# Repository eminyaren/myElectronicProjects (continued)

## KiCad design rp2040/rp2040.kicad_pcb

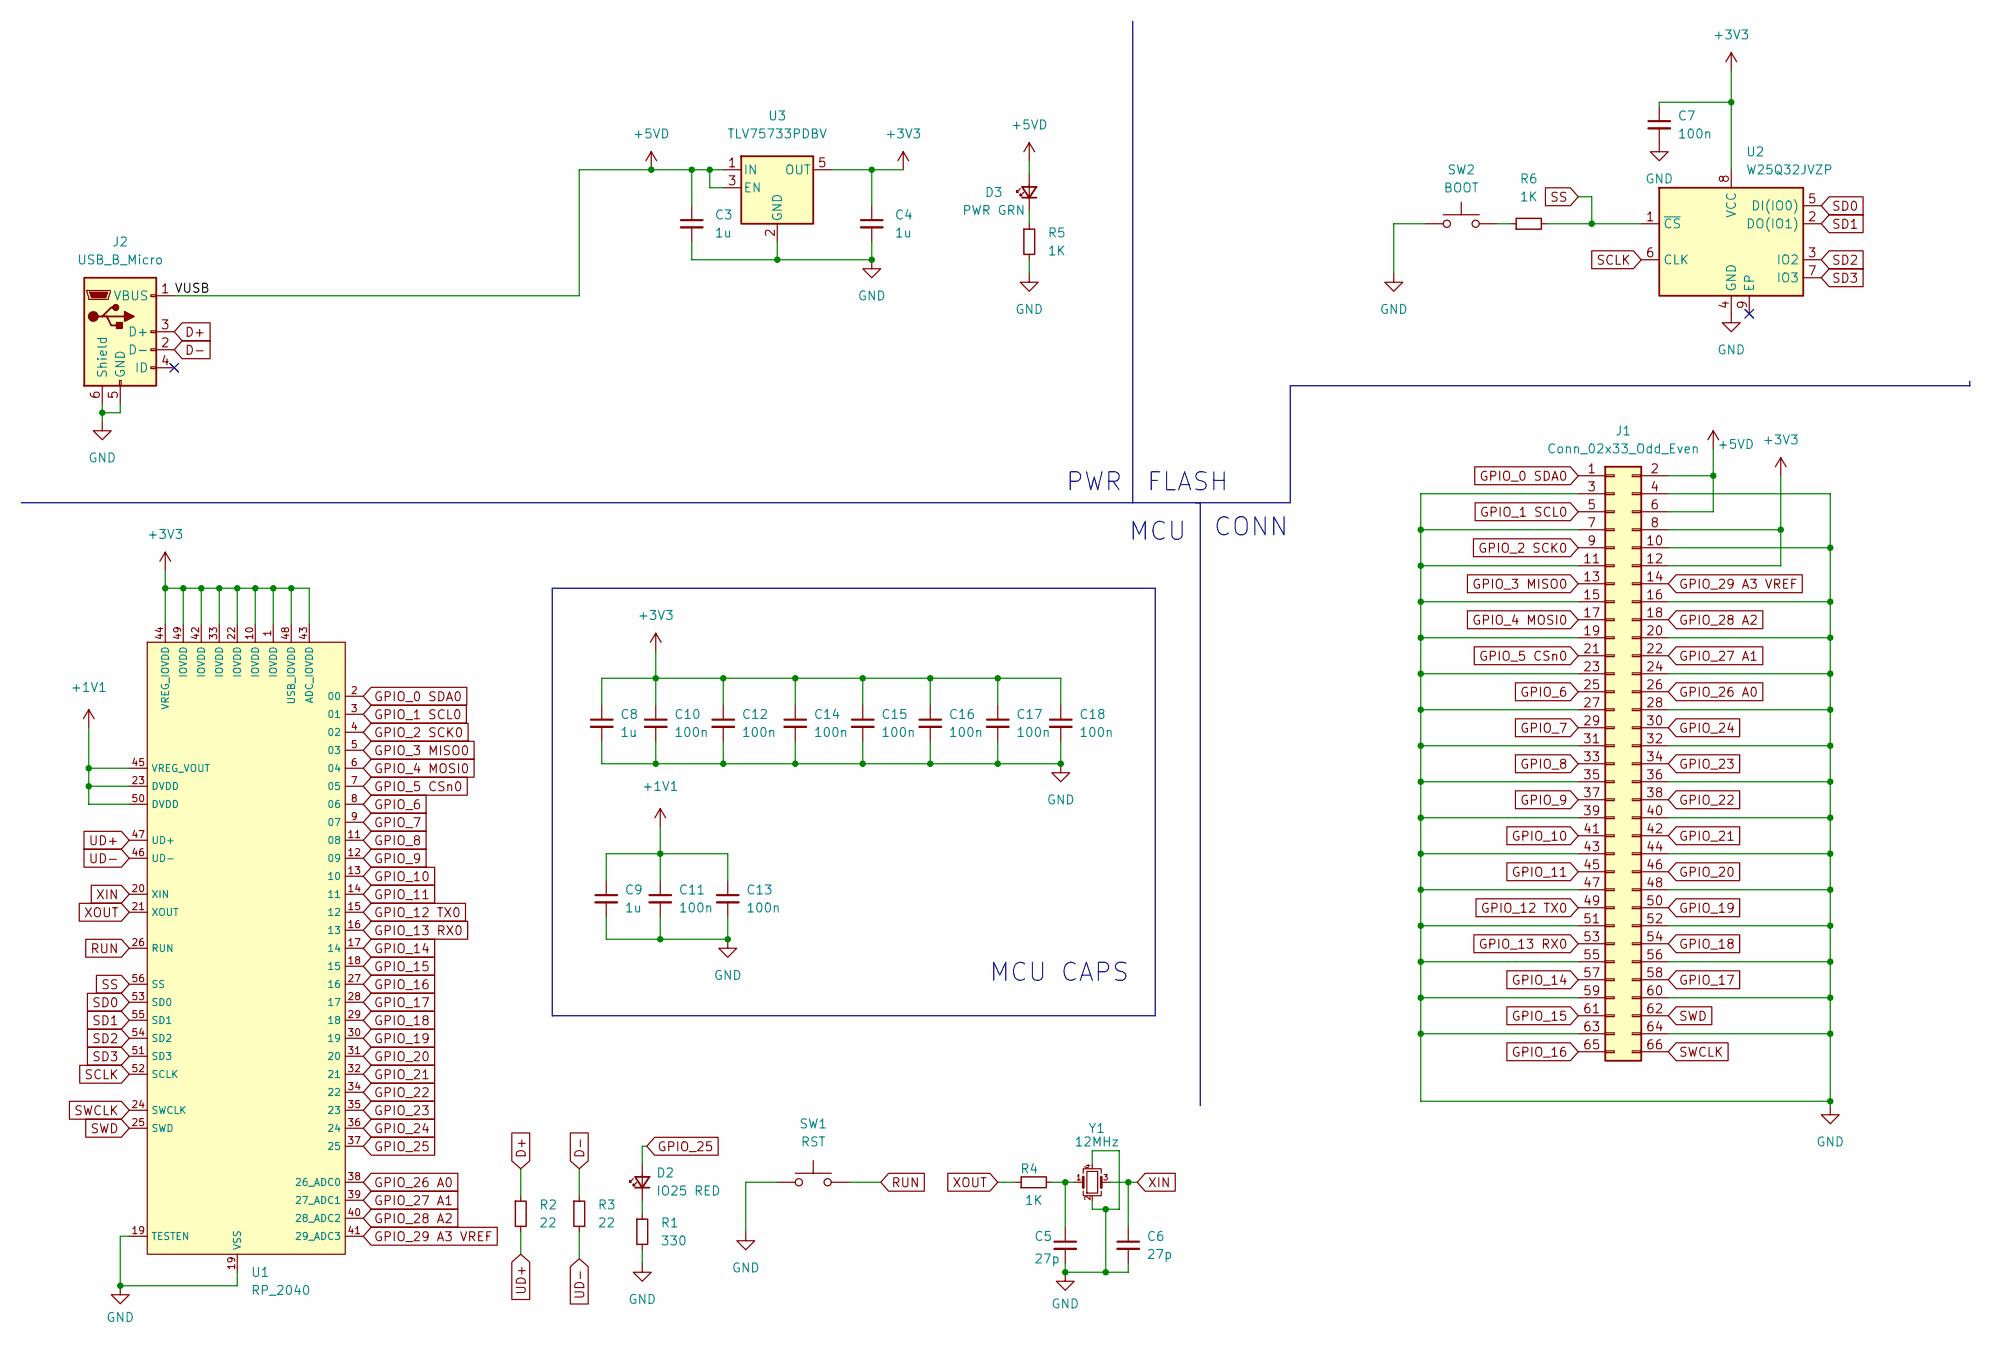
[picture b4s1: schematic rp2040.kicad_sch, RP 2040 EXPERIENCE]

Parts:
C3, C4: 1u; CP_EIA-1608-08_AVX-J
C5, C6: 27p; C_0402_1005Metric
C7, C10, C11, C12, C13, C14, C15, C16, C17, C18: 100n; C_0402_1005Metric
C8, C9: 1u; C_0603_1608Metric
D2: IO25 RED; LED_0201_0603Metric
D3: PWR GRN; LED_0201_0603Metric
J1: Conn_02x33_Odd_Even; PinHeader_2x33_P2.54mm_Horizontal
J2: USB_B_Micro; USB_Micro-B_Molex_47346-0001
R1: 330; R_0402_1005Metric
R2, R3: 22; R_0402_1005Metric
R4, R5, R6: 1K; R_0402_1005Metric
SW1: RST; SW_Push_SPST_NO_Alps_SKRK
SW2: BOOT; SW_Push_SPST_NO_Alps_SKRK
U1: RP_2040
U2: W25Q32JVZP; WSON-8-1EP_6x5mm_P1.27mm_EP3.4x4.3mm
U3: TLV75733PDBV; SOT-23-5
Y1: 12MHz; Crystal_SMD_3225-4Pin_3.2x2.5mm

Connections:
+1V1: C9.1, C11.1, C13.1, U1.23 (DVDD), U1.45 (VREG_VOUT), U1.50 (DVDD)
+3V3: C4.1, C7.1, C8.1, C10.1, C12.1, C14.1, C15.1, C16.1, C17.1, C18.1, J1.8, J1.12, U1.1 (IOVDD), U1.10 (IOVDD), U1.22 (IOVDD), U1.33 (IOVDD), U1.42 (IOVDD), U1.43 (ADC_IOVDD), U1.44 (VREG_IOVDD), U1.48 (USB_IOVDD), U1.49 (IOVDD), U2.8 (VCC), U3.5 (OUT)
+5VD: C3.1, D3.2 (A), J1.2, J1.6, J2.1 (VBUS), U3.1 (IN), U3.3 (EN)
D+: J2.3 (D+), R2.1
D-: J2.2 (D-), R3.1
GND: C3.2, C4.2, C5.2, C6.2, C7.2, C8.2, C9.2, C10.2, C11.2, C12.2, C13.2, C14.2, C15.2, C16.2, C17.2, C18.2, J1.3, J1.4, J1.7, J1.10, J1.11, J1.15, J1.16, J1.19, J1.20, J1.23, J1.24, J1.27, J1.28, J1.31, J1.32, J1.35, J1.36, J1.39, J1.40, J1.43, J1.44, J1.47, J1.48, J1.51, J1.52, J1.55, J1.56, J1.59, J1.60, J1.63, J1.64, J2.5 (GND), J2.6 (Shield), R1.2, R5.2, SW1.1, SW2.1, U1.19 (TESTEN), U2.4 (GND), U3.2 (GND), Y1.2, Y1.4; also elsewhere on the board
GPIO_0 SDA0: J1.1, U1.2 (00)
GPIO_1 SCL0: J1.5, U1.3 (01)
GPIO_2 SCK0: J1.9, U1.4 (02)
GPIO_3 MISO0: J1.13, U1.5 (03)
GPIO_4 MOSI0: J1.17, U1.6 (04)
GPIO_5 CSn0: J1.21, U1.7 (05)
GPIO_6: J1.25, U1.8 (06)
GPIO_7: J1.29, U1.9 (07)
GPIO_8: J1.33, U1.11 (08)
GPIO_9: J1.37, U1.12 (09)
GPIO_10: J1.41, U1.13 (10)
GPIO_11: J1.45, U1.14 (11)
GPIO_12 TX0: J1.49, U1.15 (12)
GPIO_13 RX0: J1.53, U1.16 (13)
GPIO_14: J1.57, U1.17 (14)
GPIO_15: J1.61, U1.18 (15)
GPIO_16: J1.65, U1.27 (16)
GPIO_17: J1.58, U1.28 (17)
GPIO_18: J1.54, U1.29 (18)
GPIO_19: J1.50, U1.30 (19)
GPIO_20: J1.46, U1.31 (20)
GPIO_21: J1.42, U1.32 (21)
GPIO_22: J1.38, U1.34 (22)
GPIO_23: J1.34, U1.35 (23)
GPIO_24: J1.30, U1.36 (24)
GPIO_25: D2.2 (A), U1.37 (25)
GPIO_26 A0: J1.26, U1.38 (26_ADC0)
GPIO_27 A1: J1.22, U1.39 (27_ADC1)
GPIO_28 A2: J1.18, U1.40 (28_ADC2)
GPIO_29 A3 VREF: J1.14, U1.41 (29_ADC3)
unnamed: C5.1, R4.2, Y1.1
unnamed: D2.1 (K), R1.1
unnamed: D3.1 (K), R5.1
unnamed 39: R6.1, SW2.2; also elsewhere on the board
RUN: SW1.2, U1.26 (RUN); also elsewhere on the board
SCLK: U1.52 (SCLK), U2.6 (CLK)
SD0: U1.53 (SD0), U2.5 (DI(IO0))
SD1: U1.55 (SD1), U2.2 (DO(IO1))
SD2: U1.54 (SD2), U2.3 (IO2)
SD3: U1.51 (SD3), U2.7 (IO3)
SS: R6.2, U1.56 (SS), U2.1 (~CS)
SWCLK: J1.66, U1.24 (SWCLK)
SWD: J1.62, U1.25 (SWD)
UD+: R2.2, U1.47 (UD+)
UD-: R3.2, U1.46 (UD-)
XIN: C6.1, U1.20 (XIN), Y1.3
XOUT: R4.1, U1.21 (XOUT)

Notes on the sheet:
FLASH
MCU
PWR
MCU CAPS
CONN

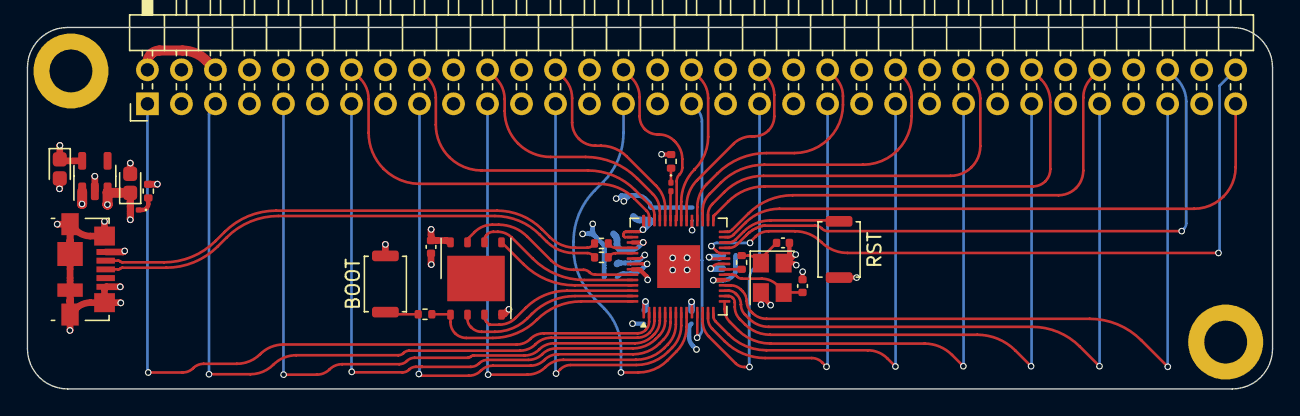
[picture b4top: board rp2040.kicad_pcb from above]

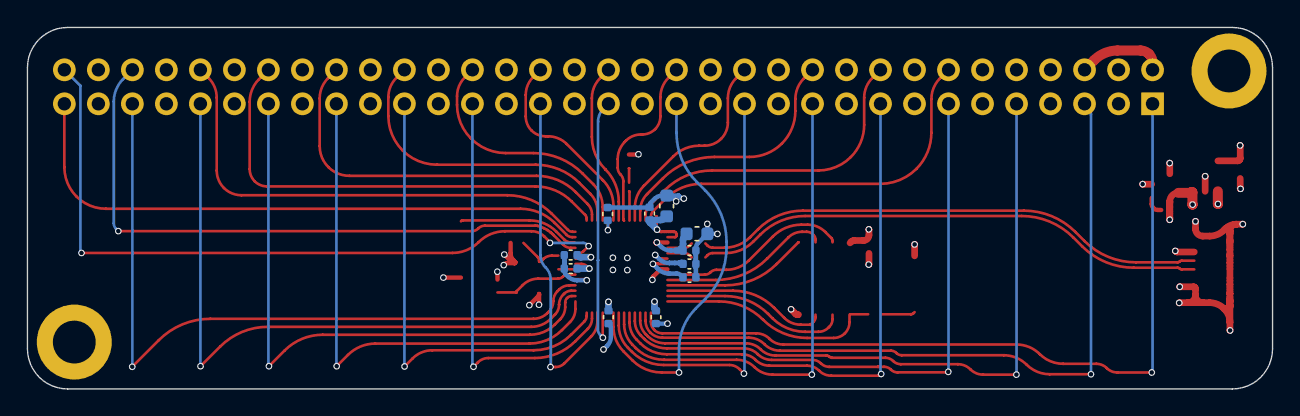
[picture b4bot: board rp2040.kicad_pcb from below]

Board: 4 copper layers, 93.0 x 27.0 mm, 32 parts (11 on the bottom side), 53 nets.

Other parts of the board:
BOOT: BOOT; SW_Push_SPST_NO_Alps_SKRK
RST: RST; SW_Push_SPST_NO_Alps_SKRK

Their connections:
GND: BOOT.1, RST.1; also elsewhere on the board
unnamed 39: BOOT.2; also elsewhere on the board
RUN: RST.2; also elsewhere on the board

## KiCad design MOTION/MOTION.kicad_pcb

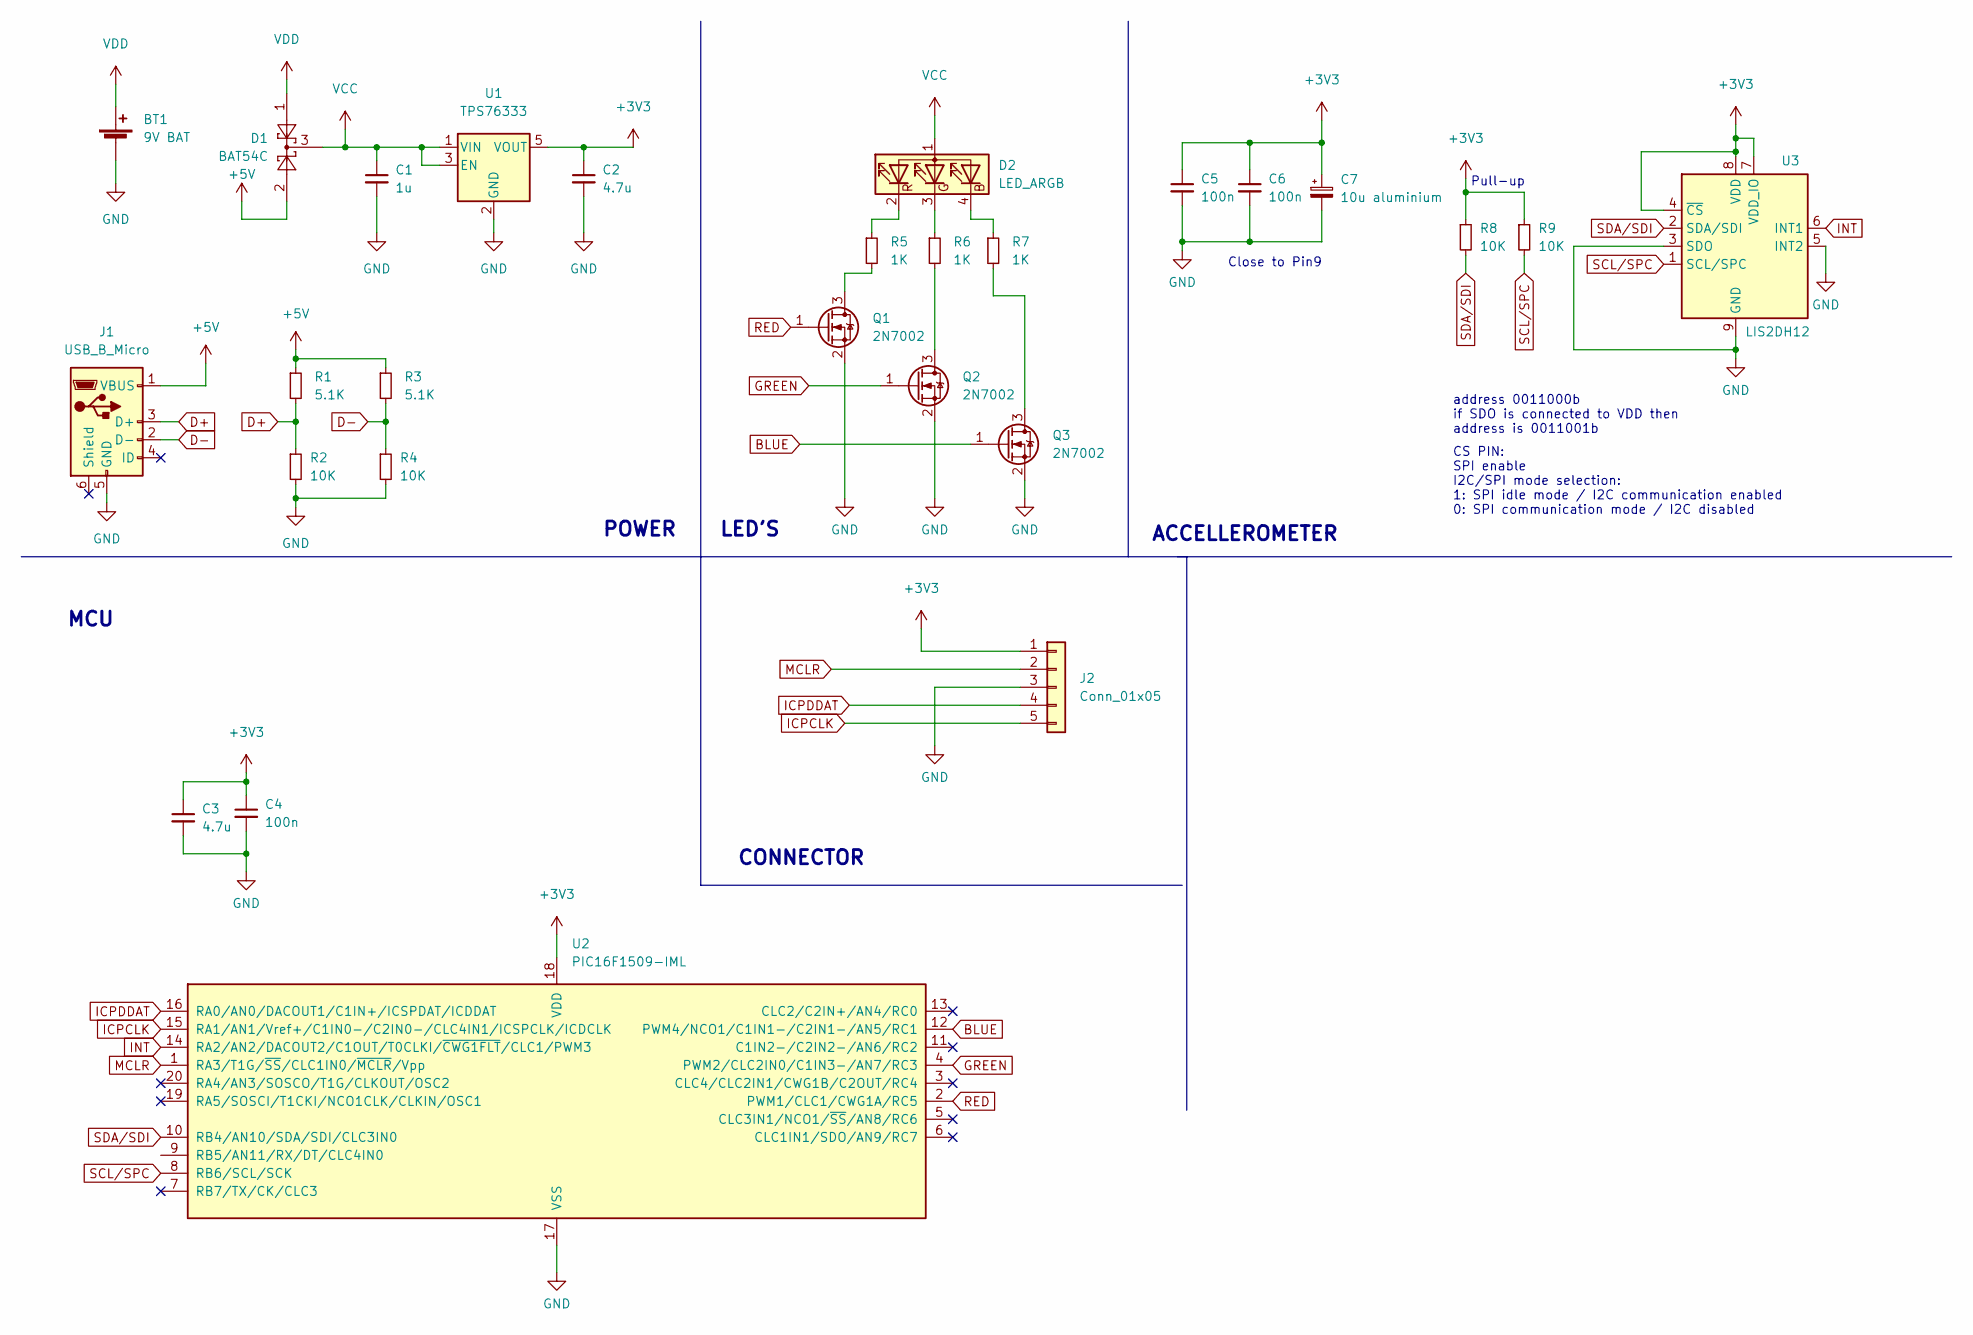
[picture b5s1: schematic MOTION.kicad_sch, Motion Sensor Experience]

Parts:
BT1: 9V BAT; PinHeader_1x02_P2.54mm_Vertical
C1: 1u; CP_EIA-1608-08_AVX-J
C2, C3: 4.7u; CP_EIA-1608-08_AVX-J
C4, C5, C6: 100n; C_0402_1005Metric
C7: 10u aluminium; CP_EIA-1608-08_AVX-J
D1: BAT54C; SOT-23
D2: LED_ARGB; LED_RGB_1210
J1: USB_B_Micro; USB_Micro-B_Molex_47346-0001
J2: Conn_01x05; PinHeader_1x05_P2.54mm_Horizontal
Q1, Q2, Q3: 2N7002; SOT-23
R1, R3: 5.1K; R_0402_1005Metric
R2, R4, R8, R9: 10K; R_0402_1005Metric
R5, R6, R7: 1K; R_0402_1005Metric
U1: TPS76333; SOT-23-5
U2: PIC16F1509-IML; QFN-20-1EP_4x4mm_P0.5mm_EP2.7x2.7mm
U3: LIS2DH12; LGA-14_2x2mm_P0.35mm_LayoutBorder3x4y

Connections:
+3V3: C2.1, C3.1, C4.1, C5.1, C6.1, C7.1, J2.1, R8.1, R9.1, U1.5 (VOUT), U2.18 (VDD), U3.4 (~CS), U3.7 (VDD_IO), U3.8 (VDD)
+5V: D1.2, J1.1 (VBUS), R1.1, R3.1
BLUE: Q3.1 (G), U2.12 (PWM4/NCO1/C1IN1-/C2IN1-/AN5/RC1)
D+: J1.3 (D+), R1.2, R2.1
D-: J1.2 (D-), R3.2, R4.1
GND: BT1.2 (-), C1.2, C2.2, C3.2, C4.2, C5.2, C6.2, C7.2, J1.5 (GND), J2.3, Q1.2 (S), Q2.2 (S), Q3.2 (S), R2.2, R4.2, U1.2 (GND), U2.17 (VSS), U3.3 (SDO), U3.5 (INT2), U3.9 (GND), U3.10 (GND), U3.11 (GND), U3.12 (GND), U3.13 (GND), U3.14 (GND)
GREEN: Q2.1 (G), U2.4 (PWM2/CLC2IN0/C1IN3-/AN7/RC3)
ICPCLK: J2.5, U2.15 (RA1/AN1/Vref+/C1IN0-/C2IN0-/CLC4IN1/ICS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)
ICPDDAT: J2.4, U2.16 (RA0/AN0/DACOUT1/C1IN+/ICSPDAT/ICDDAT)
INT: U2.14 (RA2/AN2/DACOUT2/C1OUT/T0CLKI/~CWG1FLT/C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), U3.6 (INT1)
MCLR: J2.2, U2.1 (RA3/T1G/~SS/CLC1IN0/~MCLR/Vpp)
unnamed: D2.2 (RK), R5.1
unnamed: D2.3 (GK), R6.1
unnamed: D2.4 (BK), R7.1
unnamed: Q1.3 (D), R5.2
unnamed: Q2.3 (D), R6.2
unnamed: Q3.3 (D), R7.2
RED: Q1.1 (G), U2.2 (PWM1/CLC1/CWG1A/RC5)
SCL/SPC: R9.2, U2.8 (RB6/SCL/SCK), U3.1 (SCL/SPC)
SDA/SDI: R8.2, U2.10 (RB4/AN10/SDA/SDI/CLC3IN0), U3.2 (SDA/SDI)
VCC: C1.1, D1.3, D2.1 (A), U1.1 (VIN), U1.3 (EN)
VDD: BT1.1 (+), D1.1

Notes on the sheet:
MCU
Pull-up
POWER
ACCELLEROMETER
Close to Pin9
LED'S
address 0011000b if SDO is connected to VDD then address is 0011001b
CS PIN: SPI enable I2C/SPI mode selection: 1: SPI idle mode / I2C communication enabled 0: SPI communication mode / I2C disabled
CONNECTOR

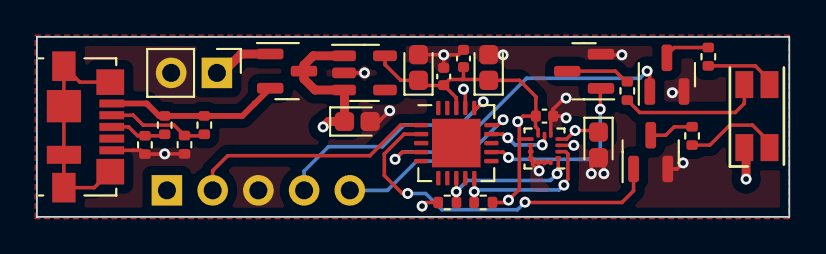
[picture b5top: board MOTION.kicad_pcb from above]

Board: 4 copper layers, 41.8 x 10.0 mm, 27 parts (1 on the bottom side), 22 nets.

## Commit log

2022-06-24 Adding RP2040 KiCad Project
2022-07-04 Gimble Project
2022-07-04 Projects
